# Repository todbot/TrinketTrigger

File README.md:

# TrinketTrigger

The simplest Eurorack module?  

Trinket M0 with capsense buttons sending 3.3V CV & gate.

Button '~ A ~' is analog out (CV). Button 'B' is on/off (gate).

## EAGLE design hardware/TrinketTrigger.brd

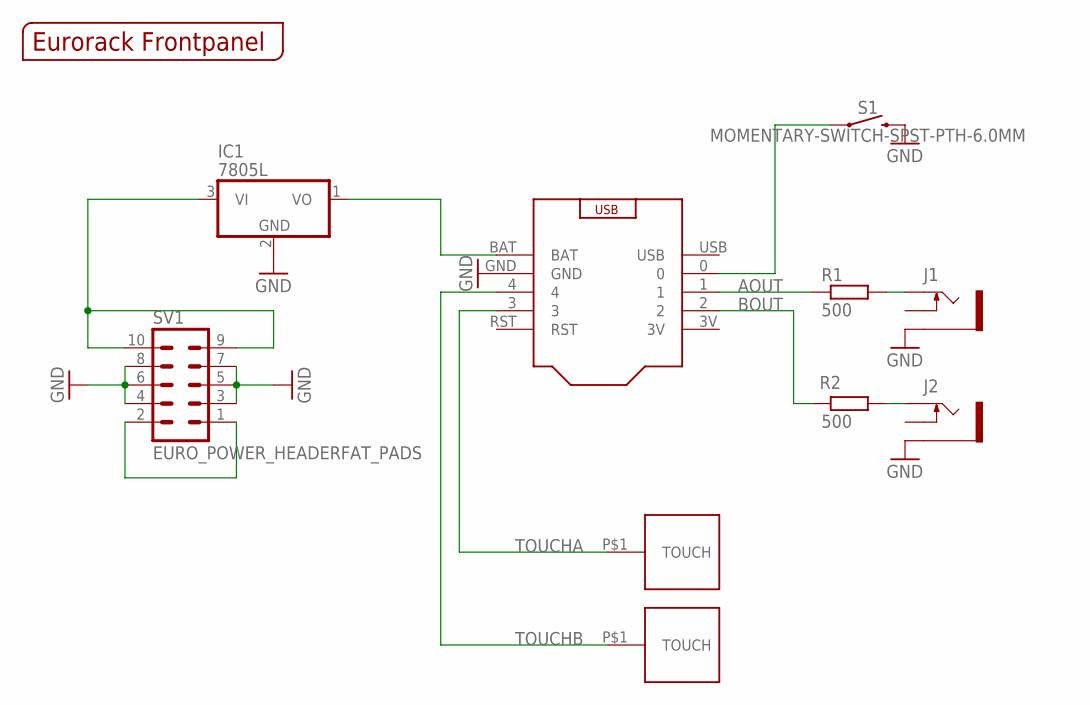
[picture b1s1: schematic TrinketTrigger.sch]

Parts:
IC1: 7805L; TO92
J1, J2: THONKICONNNEW; WQP-PJ301M-12_JACK
R1, R2: 500; 0204/7
S1: MOMENTARY-SWITCH-SPST-PTH-6.0MM; TACTILE_SWITCH_PTH_6.0MM
SV1: EURO_POWER_HEADERFAT_PADS; EURO_PWR_HEADER_FAT
TOUCHA: TOUCHPADA
TOUCHB: TOUCHPADA
U$1: EURORACK_PANEL6HP; EURORACK6HPPANEL
U$2: TRINKETM0NH; TRINKETMO_NOHOLES

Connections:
AOUT: R1.1, U$2.1
BOUT: R2.1, U$2.2
GND: IC1.2 (GND), J1.P$3_SLEEVE (SLEEVE), J2.P$3_SLEEVE (SLEEVE), S1.3 (2), SV1.3, SV1.4, SV1.5, SV1.6, SV1.7, SV1.8, U$2.GND
unnamed: J1.P$1_TIP (TIP), R1.2
unnamed: SV1.1, SV1.2
unnamed: S1.1, U$2.0
unnamed: J2.P$1_TIP (TIP), R2.2
unnamed: IC1.1 (VO), U$2.BAT
unnamed: IC1.3 (VI), SV1.9, SV1.10
TOUCHA: TOUCHA.P$1, U$2.3
TOUCHB: TOUCHB.P$1, U$2.4

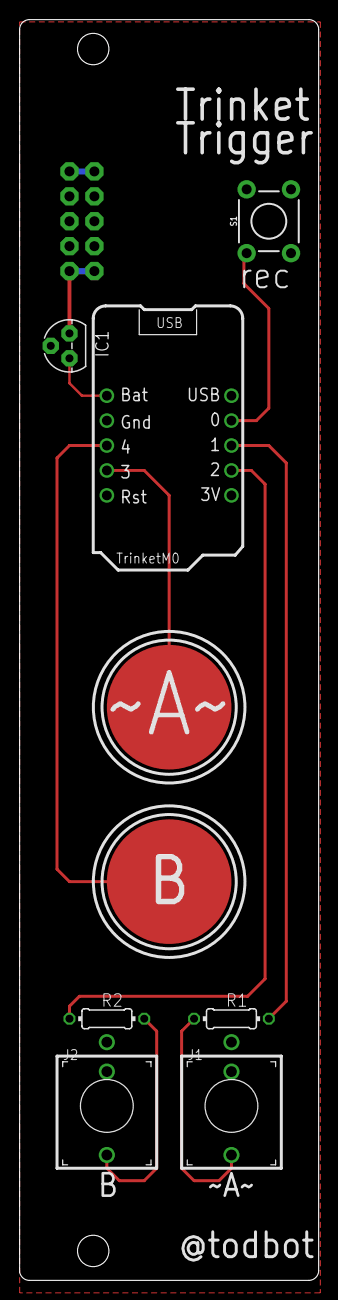
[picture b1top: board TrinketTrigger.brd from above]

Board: 2 copper layers, 30.5 x 128.5 mm, 11 parts (1 on the bottom side), 11 nets.

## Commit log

2020-05-19 first commit, moved from TrinketTouringMachine
2020-05-19 added img
2020-05-19 commit actual real firmware
2020-08-13 added rec button support
2020-08-13 added sch pdf
2021-09-03 added tap tempo example
2021-09-03 add ability to set gate duration by tap hold duration
2021-09-03 make tap tempo variant actually useful

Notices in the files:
parts and their libraries:
SparkFun-Switches: Licensing: Creative Commons ShareAlike 4.0 International - https://creativecommons.org/licenses/by-sa/4.0
